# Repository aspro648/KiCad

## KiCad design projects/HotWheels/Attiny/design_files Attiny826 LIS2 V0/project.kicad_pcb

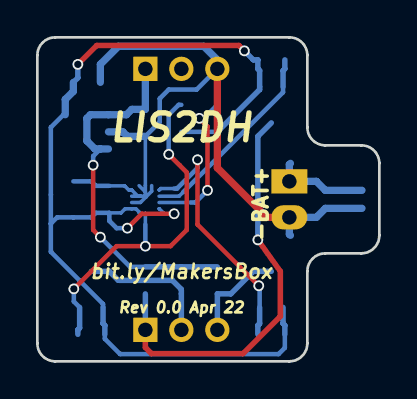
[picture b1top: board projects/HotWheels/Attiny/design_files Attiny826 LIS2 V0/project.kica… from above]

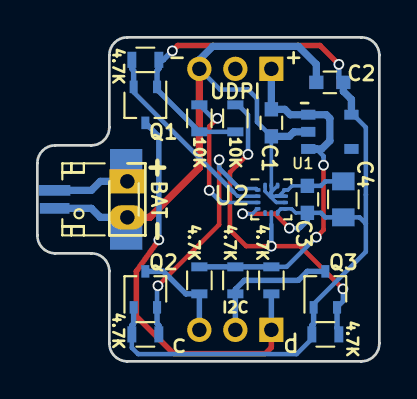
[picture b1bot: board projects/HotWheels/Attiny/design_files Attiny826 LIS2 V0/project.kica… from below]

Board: 2 copper layers, 19.0 x 18.0 mm, 21 parts (21 on the bottom side), 11 nets.

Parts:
C1, C2, C3: 0.1uF; C_0603
C4: 10uF; C_0805
J1: JST-SH; JST_SH_SM02B_hand_solder
J2: BAT; PIN_HEADER_LED
J4: UDPI; PinHeader_1x03_P2.00mm_Vertical
J8: I2C; PinHeader_1x03_P2.00mm_Vertical
Q1, Q2, Q3: BSS138; SOT-323_SC-70
R1, R2, R3, R4, R5, R6: 4.7K; R_0603
R7, R8: 10K; R_0603
U1: Linear 3.3V; SOT-753
U2: LIS2DH; LGA-14_2x2mm_P0.35mm_LayoutBorder3x4y

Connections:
+3V3: C2.1, C3.1, C4.1, Q1.1, Q2.1, Q3.1, R4.1, R5.1, R6.1, R7.1, R8.1, U1.5, U2.4, U2.7, U2.8
/INT: J8.2, Q3.3, R3.2
/INT_3V3: Q3.2, R6.2, R8.2, U2.6
/SCL: J8.3, Q2.3, R2.2
/SCL_3V3: Q2.2, R5.2, U2.1
/SDA: J8.1, Q1.3, R1.2
/SDA_3V3: Q1.2, R4.2, U2.2
GND: C1.2, C2.2, C3.2, C4.2, J1.1, J2.2, J4.3, U1.2, U2.9, U2.10, U2.11, U2.12, U2.13, U2.14
unnamed: J1.2, J2.1
unnamed: R7.2, U2.3
VCC: C1.1, J4.1, R1.1, R2.1, R3.1, U1.1, U1.3

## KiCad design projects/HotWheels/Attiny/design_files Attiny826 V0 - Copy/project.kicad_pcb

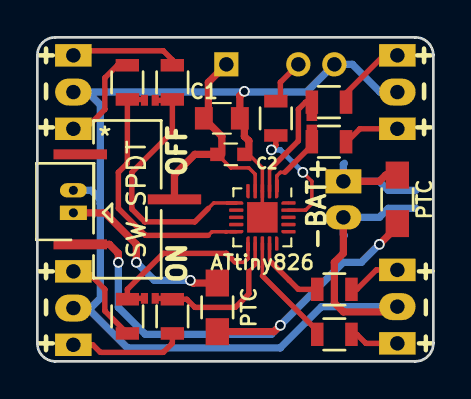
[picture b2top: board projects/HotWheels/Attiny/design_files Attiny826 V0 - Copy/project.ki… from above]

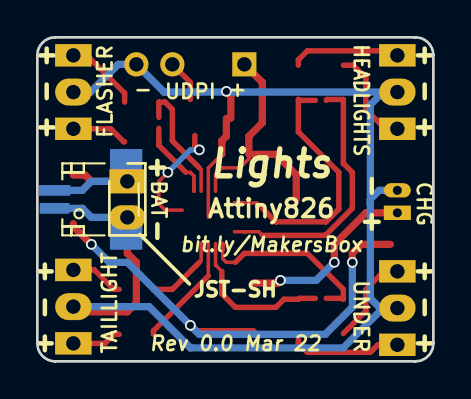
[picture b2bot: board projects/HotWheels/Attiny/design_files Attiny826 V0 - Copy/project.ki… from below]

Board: 2 copper layers, 22.0 x 18.0 mm, 26 parts (3 on the bottom side), 23 nets.

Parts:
C1: 10uF; C_0805
C2: 0.1uF; C_0603
F1, F2: PTC; R_0805_HandSoldering
J1: JST-SH; JST_SH_SM02B_hand_solder
J2: BAT; PIN_HEADER_LED
J3: CHG; Connector_Molex_PicoBlade_53047-0210
J4: UDPI; UDPI_header
J5: HL; Pin_Header_THD_1x03
J6: TL; Pin_Header_THD_1x03
J7: FL; Pin_Header_THD_1x03
J8: UL; Pin_Header_THD_1x03
JP1, JP2, JP3: SolderJumper_2_Open; Jumper
R1, R2, R3, R4, R5, R6, R7, R8, R9: 100; R_0805
SW1: SW_SPDT; JS102011SCQN
U1: ATtiny826; VQFN-20-1EP_3x3mm_P0.4mm_EP1.7x1.7mm

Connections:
/D1: JP1.1, R2.1, U1.6
/D5: JP1.2, R3.1, U1.10
/D6: JP3.1, R8.1, U1.11
/D7: JP3.2, R9.1, U1.12
/D8: R4.1, U1.13
/D9: R5.1, U1.14
/D15: JP2.2, R7.1, U1.1
/D16: JP2.1, R6.1, U1.2
/UPDI: R1.1, U1.19
GND: C1.2, C2.2, J1.1, J2.2, J3.2, J4.4, J5.2, J6.2, J7.2, J8.2, U1.3, U1.21
unnamed: F1.1, J3.1
unnamed: F1.2, F2.2, SW1.3
unnamed: F2.1, J1.2, J2.1
unnamed: J4.3, R1.2
unnamed: J5.1, R2.2
unnamed: J5.3, R3.2
unnamed: J6.1, R4.2
unnamed: J6.3, R5.2
unnamed: J7.1, R6.2
unnamed: J7.3, R7.2
unnamed: J8.1, R8.2
unnamed: J8.3, R9.2
VCC: C1.1, C2.1, J4.1, SW1.2, U1.4

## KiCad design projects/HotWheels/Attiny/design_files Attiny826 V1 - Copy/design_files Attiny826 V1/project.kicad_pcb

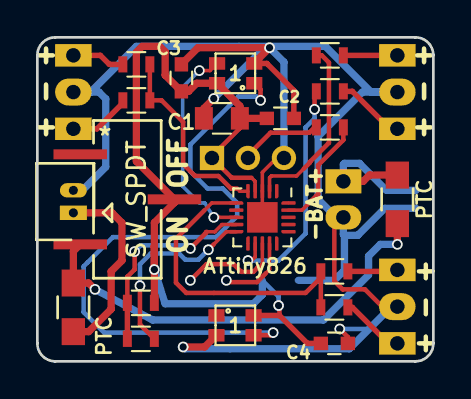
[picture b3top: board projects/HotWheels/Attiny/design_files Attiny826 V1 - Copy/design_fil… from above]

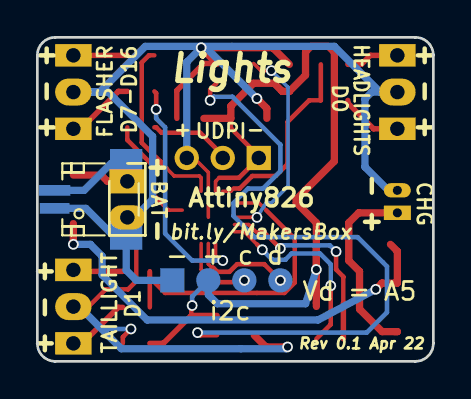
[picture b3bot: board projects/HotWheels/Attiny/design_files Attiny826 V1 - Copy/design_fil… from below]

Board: 2 copper layers, 22.0 x 18.0 mm, 27 parts (4 on the bottom side), 23 nets.

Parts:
C1: 10uF; C_0805
C2: 0.1uF; C_0603
C3, C4: 1uF; C_0603
D0, D7: SK6812MINI; WS2812B-2020
F1, F2: PTC; R_0805_HandSoldering
J1: JST-SH; JST_SH_SM02B_hand_solder
J2: BAT; PIN_HEADER_LED
J3: CHG; Connector_Molex_PicoBlade_53047-0210
J4: UDPI; PinHeader_1x03_P2.00mm_Vertical
J5: HL; Pin_Header_THD_1x03
J6: TL; Pin_Header_THD_1x03
J7: FL; Pin_Header_THD_1x03
J8: i2c; PinHeader_1x04_P2.00mm_Vertical
R1: 1; R_0603
R2: 2; R_0603
R3, R4, R5, R6, R7, R10, R11: 100; R_0603
SW1: SW_SPDT; JS102011SCQN
U1: ATtiny826; VQFN-20-1EP_3x3mm_P0.4mm_EP1.7x1.7mm

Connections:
/D0: R3.1, R11.1, U1.5
/D1: R4.1, R5.1, U1.6
/D3: D0.3, U1.8
/D4: R1.2, R2.1, U1.9
/D5: R2.2, U1.10
/D7: R7.1, U1.12
/D16: R6.1, U1.2
/SCL: J8.3, U1.14
/SDA: J8.4, U1.13
/UPDI: R10.1, U1.19
GND: C1.2, C2.2, C3.2, C4.2, D0.2, D7.2, J1.1, J2.2, J3.2, J4.3, J5.2, J6.2, J7.2, J8.1, U1.3, U1.21
unnamed: D0.1, D7.3
unnamed: F1.1, J3.1
unnamed: F1.2, F2.2, SW1.3
unnamed: F2.1, J1.2, J2.1
unnamed: J4.2, R10.2
unnamed: J5.1, R11.2
unnamed: J5.3, R3.2
unnamed: J6.1, R4.2
unnamed: J6.3, R5.2
unnamed: J7.1, R6.2
unnamed: J7.3, R7.2
VCC: C1.1, C2.1, C3.1, C4.1, D0.4, D7.4, J4.1, J8.2, R1.1, SW1.2, U1.4

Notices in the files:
parts and their libraries:
Copyright 2016 Accelerated Designs. All rights reserved.
